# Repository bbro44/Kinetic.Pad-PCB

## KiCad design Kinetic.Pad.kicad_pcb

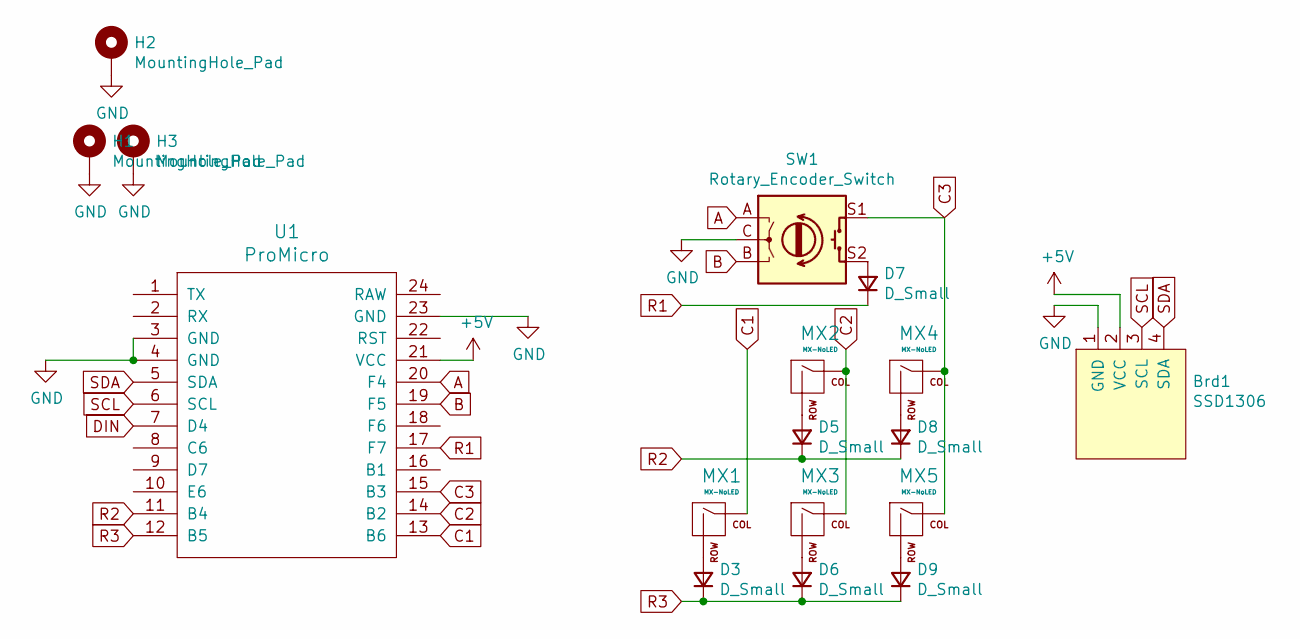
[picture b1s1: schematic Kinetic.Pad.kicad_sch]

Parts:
Brd1: SSD1306; SSD1306-0.91-OLED-4pin-128x32
D3, D5, D6, D7, D8, D9: D_Small; D_DO-35_SOD27_P7.62mm_Horizontal
H1, H2, H3: MountingHole_Pad; MountingHole_2.5mm_Pad
MX1, MX2, MX3, MX4, MX5: MX-NoLED; MXOnly-1U-NoLED
SW1: Rotary_Encoder_Switch; RotaryEncoder_EC11
U1: ProMicro; ArduinoProMicro

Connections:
+5V: Brd1.2 (VCC), U1.21 (VCC); also elsewhere on the board
A: SW1.A, U1.20 (F4)
B: SW1.B, U1.19 (F5)
C1: MX1.1 (COL), U1.13 (B6)
C2: MX2.1 (COL), MX3.1 (COL), U1.14 (B2)
C3: MX4.1 (COL), MX5.1 (COL), SW1.S1, U1.15 (B3)
DIN: U1.7 (D4)
GND: Brd1.1 (GND), H1.1, H2.1, H3.1, SW1.C, U1.3 (GND), U1.4 (GND), U1.23 (GND); also elsewhere on the board
unnamed: D3.2 (A), MX1.2 (ROW)
unnamed: D5.2 (A), MX2.2 (ROW)
unnamed: D6.2 (A), MX3.2 (ROW)
unnamed: D7.2 (A), SW1.S2
unnamed: D8.2 (A), MX4.2 (ROW)
unnamed: D9.2 (A), MX5.2 (ROW)
R1: D7.1 (K), U1.17 (F7)
R2: D5.1 (K), D8.1 (K), U1.11 (B4)
R3: D3.1 (K), D6.1 (K), D9.1 (K), U1.12 (B5)
SCL: Brd1.3 (SCL), U1.6 (SCL); also elsewhere on the board
SDA: Brd1.4 (SDA), U1.5 (SDA); also elsewhere on the board

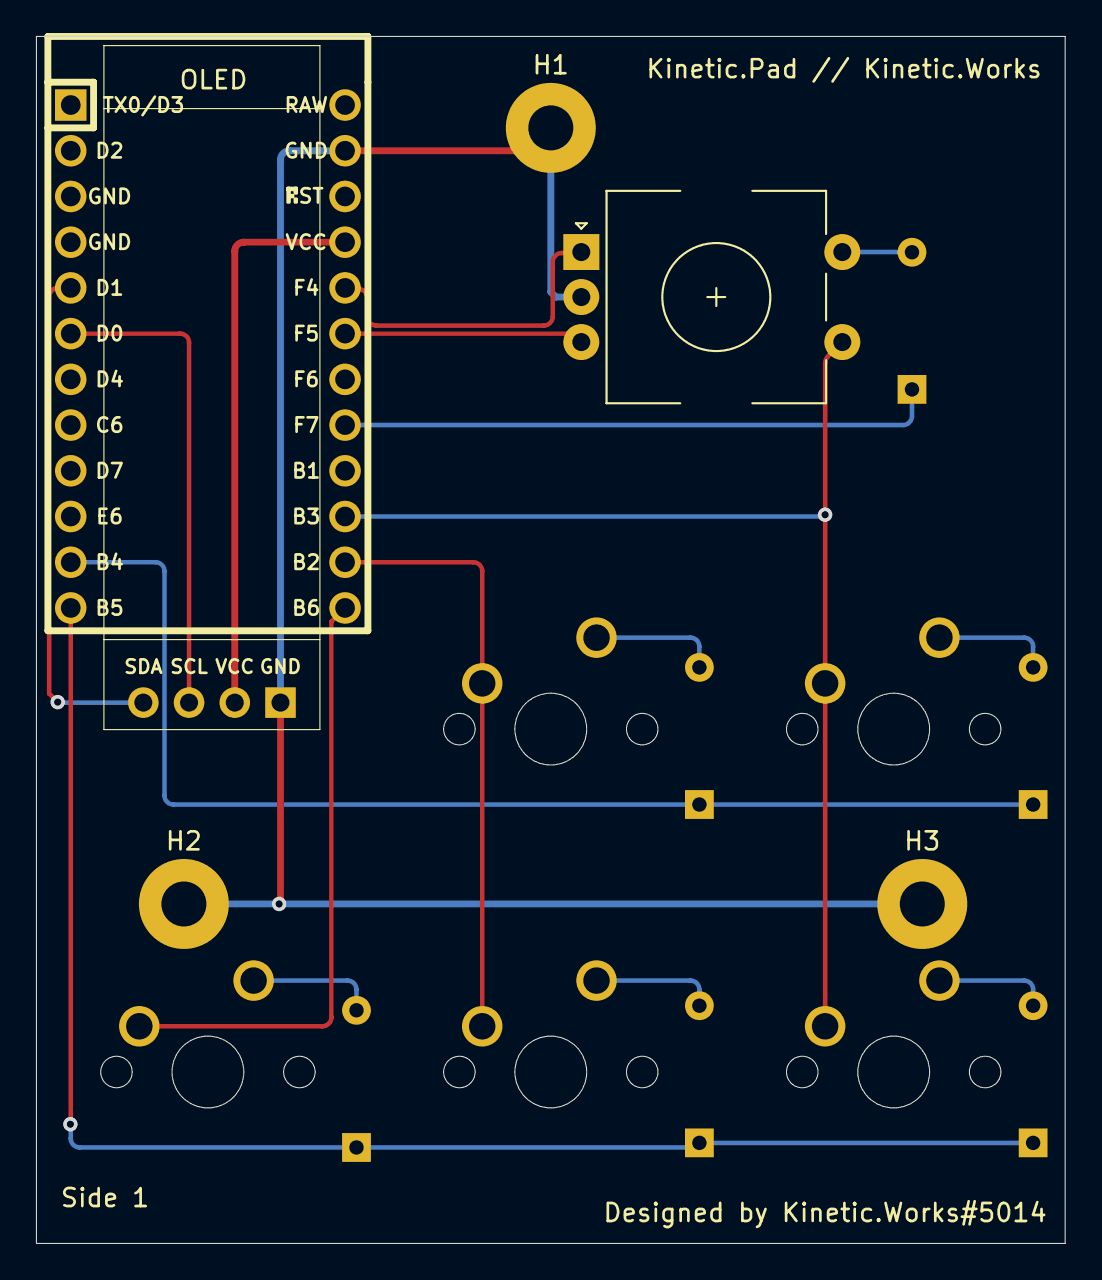
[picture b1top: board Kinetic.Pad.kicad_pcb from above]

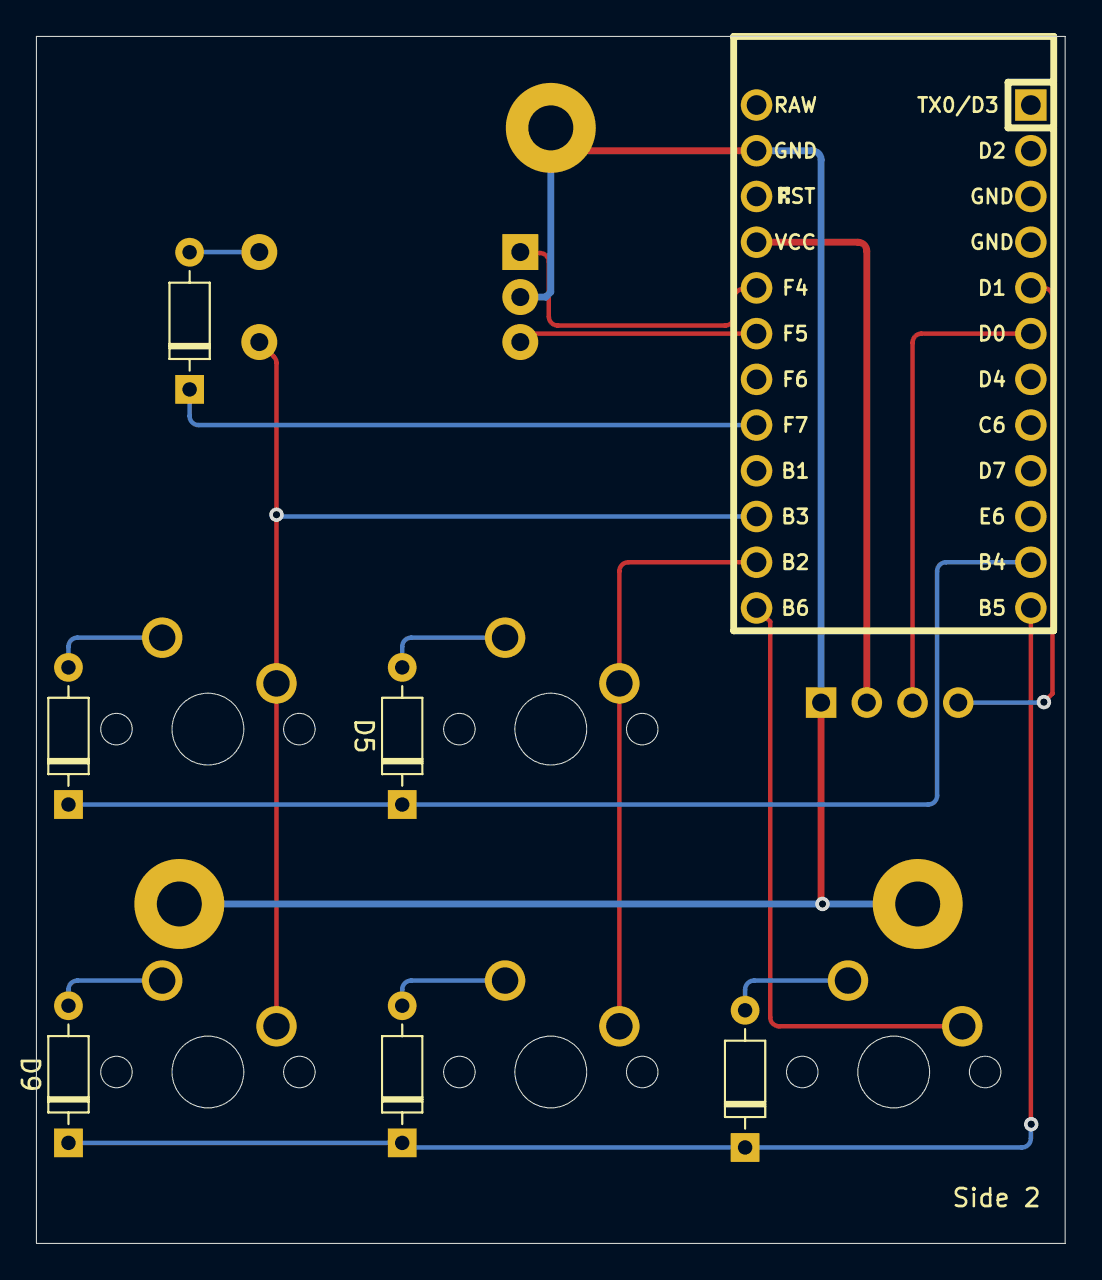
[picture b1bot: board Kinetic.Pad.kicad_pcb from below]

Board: 2 copper layers, 57.2 x 67.1 mm, 17 parts (6 on the bottom side), 18 nets.

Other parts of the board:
OLED: SSD1306; SSD1306-0.91-OLED-4pin-128x32

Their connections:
+5V: OLED.2 (VCC); also elsewhere on the board
GND: OLED.1 (GND); also elsewhere on the board
SCL: OLED.3 (SCL); also elsewhere on the board
SDA: OLED.4 (SDA); also elsewhere on the board

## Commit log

2021-11-30 Kicad Files
2021-11-30 Add Libraries
2021-11-30 Gerbers
2021-12-01 Updated MX Libraries
2021-12-01 Switched Libraries, Deleted Old Gerbers, Deleted Old Step FIle
2021-12-02 Removed Old Gerbers
2021-12-02 Nothing Important
2021-12-02 Nightly Files
2021-12-02 Add Gerbers
2021-12-09 Zip file added for gerbers
